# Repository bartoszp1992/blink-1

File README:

Go to project settings>C/C++ Build>Settings>AVR C Linker. In general, add this other arguments: "-Wl,-u,vfprintf " In Libraries, add "m" and "printf_flt". 
CPU freq: 2x8MHz
uC: 2x Atmega 328P
temp sensor: LM35 DZ probably
LM345DT

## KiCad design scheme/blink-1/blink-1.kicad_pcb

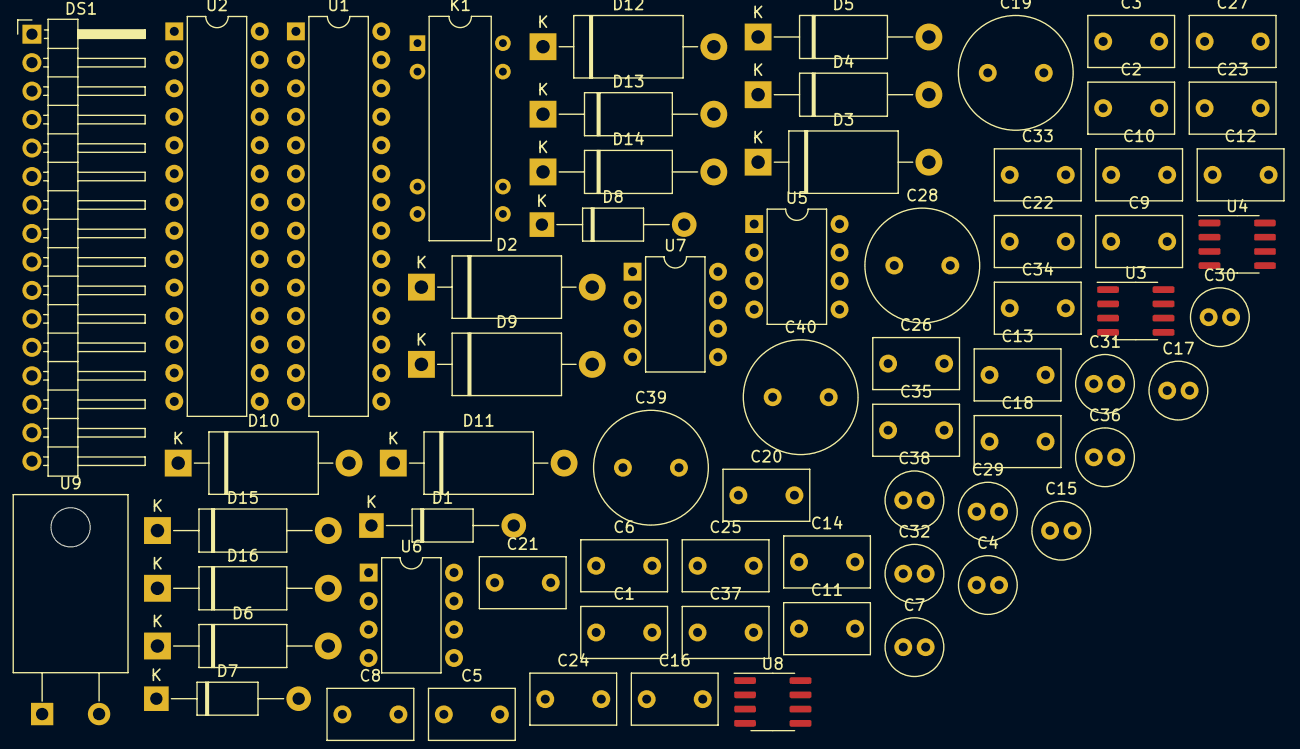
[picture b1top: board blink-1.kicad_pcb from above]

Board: 2 copper layers, 67 parts (0 on the bottom side), 54 nets, no tracks yet.

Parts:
C1, C2, C3, C5, C6, C8, C9, C10, C11, C12, C13, C14, C16, C18, C20, C21, C22, C23, C24, C25, C26, C27, C33, C34: 100n; C_Disc_D7.5mm_W4.4mm_P5.00mm
C4, C7, C15, C17, C29, C30, C31, C32, C38: 100u; C_Radial_D5.0mm_H11.0mm_P2.00mm
C19, C28, C39, C40: 100u; C_Radial_D10.0mm_H20.0mm_P5.00mm
C35: 300n; C_Disc_D7.5mm_W4.4mm_P5.00mm
C36: 1u; C_Radial_D5.0mm_H11.0mm_P2.00mm
C37: 200n; C_Disc_D7.5mm_W4.4mm_P5.00mm
D1, D7, D8: UF4004; D_DO-41_SOD81_P12.70mm_Horizontal
D2, D9, D10: 1.5KE16; D_DO-27_P15.24mm_Horizontal
D3, D11, D12: D_TVS; D_DO-27_P15.24mm_Horizontal
D4, D5, D6, D13, D14, D15, D16: SR2100; D_DO-15_P15.24mm_Horizontal
DS1: HD44780 2x16; PinHeader_1x16_P2.54mm_Horizontal
K1: 12V 40A Car; Relay_StandexMeder_DIP_LowProfile
U1, U2: ATmega328-PU; DIP-28_W7.62mm
U3: ACS712xLCTR-20A; SOIC-8_3.9x4.9mm_P1.27mm
U4: LM35-D; SOIC-8_3.9x4.9mm_P1.27mm
U5, U6, U7: IR2184; DIP-8_W7.62mm
U8: LM317L_SO8; SOIC-8_3.9x4.9mm_P1.27mm
U9: L7805; TO-220-2_Horizontal_TabDown

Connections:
+5V: C4.1, C6.1, C7.1, C8.1, C37.1, C38.1, DS1.2, DS1.4, U1.7, U2.7, U3.8, U4.8
+15V: C14.1, C15.1, C26.1, C27.1, C29.1, C30.1, C35.1, C36.1, D1.1, D7.1, D8.1, U5.5, U6.5, U7.5, U8.2, U8.3, U8.6, U8.7, U9.1
AMP: C10.1, U1.23
BAT: C11.1, U1.26
D4: DS1.13, U1.11
D5: DS1.14, U1.12
D6: DS1.15, U1.13
D7: DS1.16, U1.14
E: DS1.8, U1.6
GND: C1.2, C2.2, C3.1, C4.2, C5.1, C6.2, C7.2, C8.2, C9.2, C10.2, C11.2, C12.2, C13.2, C16.2, C19.2, C28.2, C35.2, C36.2, C37.2, C38.2, C39.2, C40.2, D5.2, D14.2, D16.2, DS1.1, DS1.3, DS1.7, U1.8, U1.22, U2.8, U2.22, U4.4, U9.2
H1: C12.1, U2.24
H2: C13.1, U2.25
H3: C16.1, U2.26
MAIN1: K1.1, K1.14
MAIN2: C19.1, C28.1, C39.1, C40.1, D4.1, D13.1, D15.1, U3.3, U3.4, U8.1
unnamed: C1.1, U1.21
unnamed: C2.1, U2.21
unnamed: C3.2, U1.20
unnamed: C5.2, U2.20
unnamed: C14.2, C15.2, C20.2, C23.2, D2.2, U5.3
unnamed: C17.1, C18.1, D1.2, U5.8
unnamed: C17.2, C18.2, D3.2, U5.6
unnamed: C20.1, U5.2
unnamed: C21.1, U6.2
unnamed: C21.2, C24.2, C26.2, C29.2, D9.2, U6.3
unnamed: C22.1, U7.2
unnamed: C22.2, C25.2, C27.2, C30.2, D10.2, U7.3
unnamed: C23.1, U5.1
unnamed: C24.1, U6.1
unnamed: C25.1, U7.1
unnamed: C31.1, C33.1, D7.2, U6.8
unnamed: C31.2, C33.2, D11.2, U6.6
unnamed: C32.1, C34.1, D8.2, U7.8
unnamed: C32.2, C34.2, D12.2, U7.6
unnamed: D2.1, U5.4
unnamed: D3.1, U5.7
unnamed: D6.1, K1.6
unnamed: D6.2, K1.2, K1.13
unnamed: D9.1, U6.4
unnamed: D10.1, U7.4
unnamed: D11.1, U6.7
unnamed: D12.1, U7.7
unnamed: K1.7, K1.8
unnamed: U3.1, U3.2
P1: U1.2, U2.10
P2: U1.3, U2.11
P3: U1.4, U2.13
P4: U1.9, U2.14
RS: DS1.6, U1.15
SPEEDO: C9.1, U1.5
TEMP: U1.28, U4.1
Uphase: D4.2, D5.1
Vphase: D13.2, D14.1
Wphase: D15.2, D16.1

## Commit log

2019-07-10 initial git release
2019-07-10 correct dir for documentation
2019-07-10 readme
